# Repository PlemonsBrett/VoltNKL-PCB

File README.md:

# VoltNKL-PCB

This repository contains all information around the Volt NKL (Nav Keyless) Keyboard.

Final Layout:

---

This repository contains:

- Schematics, PCB, and Components under `hardware/`
- Keyboard Layout, Designs, Part Lists, General Ideas under `media/`
- Firmware, and other software specific to a complete build under `software/`

guide used: https://wiki.ai03.com/books/pcb-design/page/pcb-guide-part-4---the-rest-of-the-schematic

MCU used in MacroPad: http://ww1.microchip.com/downloads/en/devicedoc/atmel-7766-8-bit-avr-atmega16u4-32u4_datasheet.pdf

MCU used in Keyboard https://www.st.com/content/st_com/en/products/microcontrollers-microprocessors/stm32-32-bit-arm-cortex-mcus/stm32-mainstream-mcus/stm32f0-series/stm32f0x2.html#tools-software

https://www.st.com/resource/en/datasheet/cd00237391.pdf

Plate Generator: http://www.keyboardcad.com/

Resources: https://keebfolio.netlify.app/tutorials

PCB GUIDE: https://wiki.ai03.com/books/pcb-design/page/pcb-guide-part-1---preparations

Plate Generator: https://kbplate.ai03.com/

Keyboard Firmware Generator: https://kbfirmware.com/

Design Tools: https://keyboard-design.com/tools.html

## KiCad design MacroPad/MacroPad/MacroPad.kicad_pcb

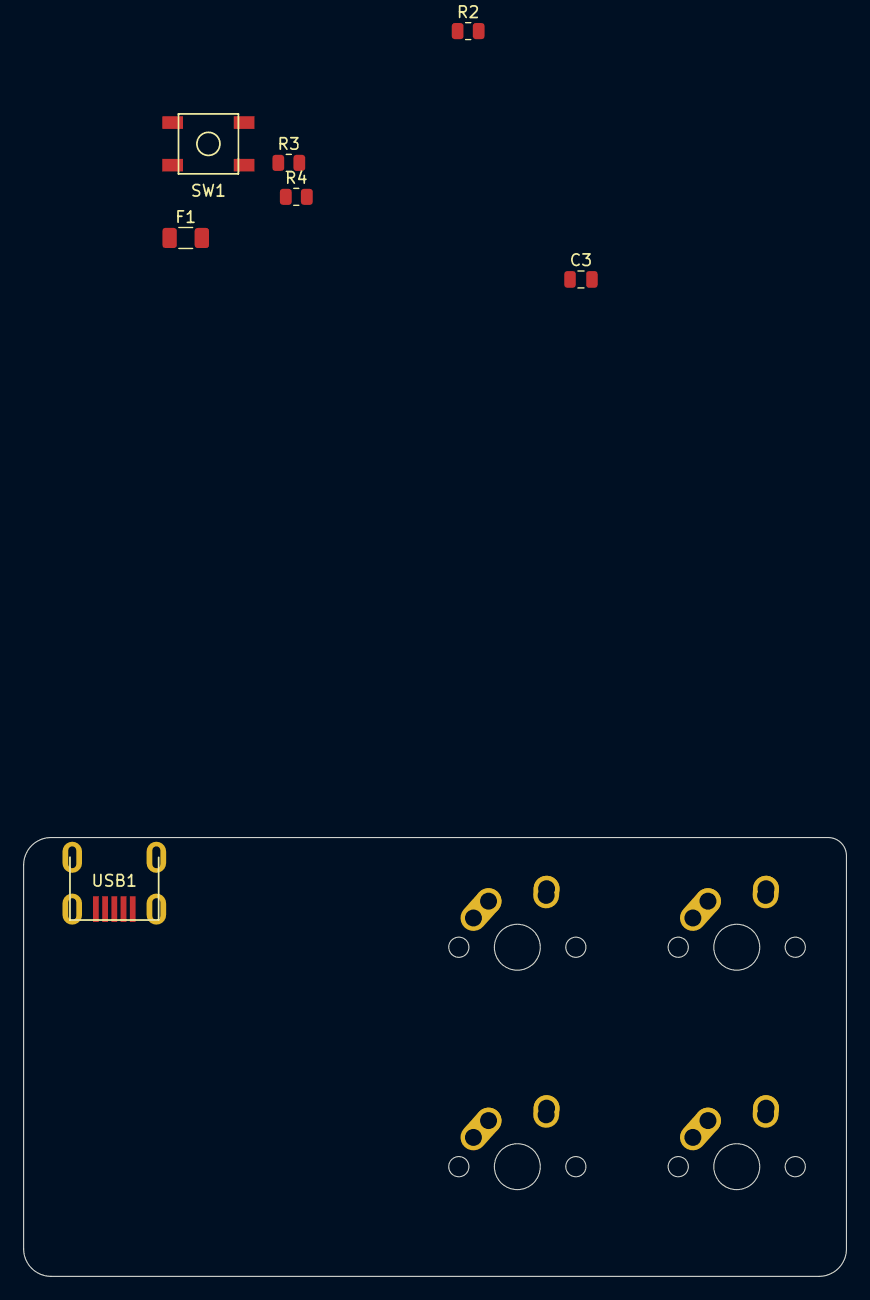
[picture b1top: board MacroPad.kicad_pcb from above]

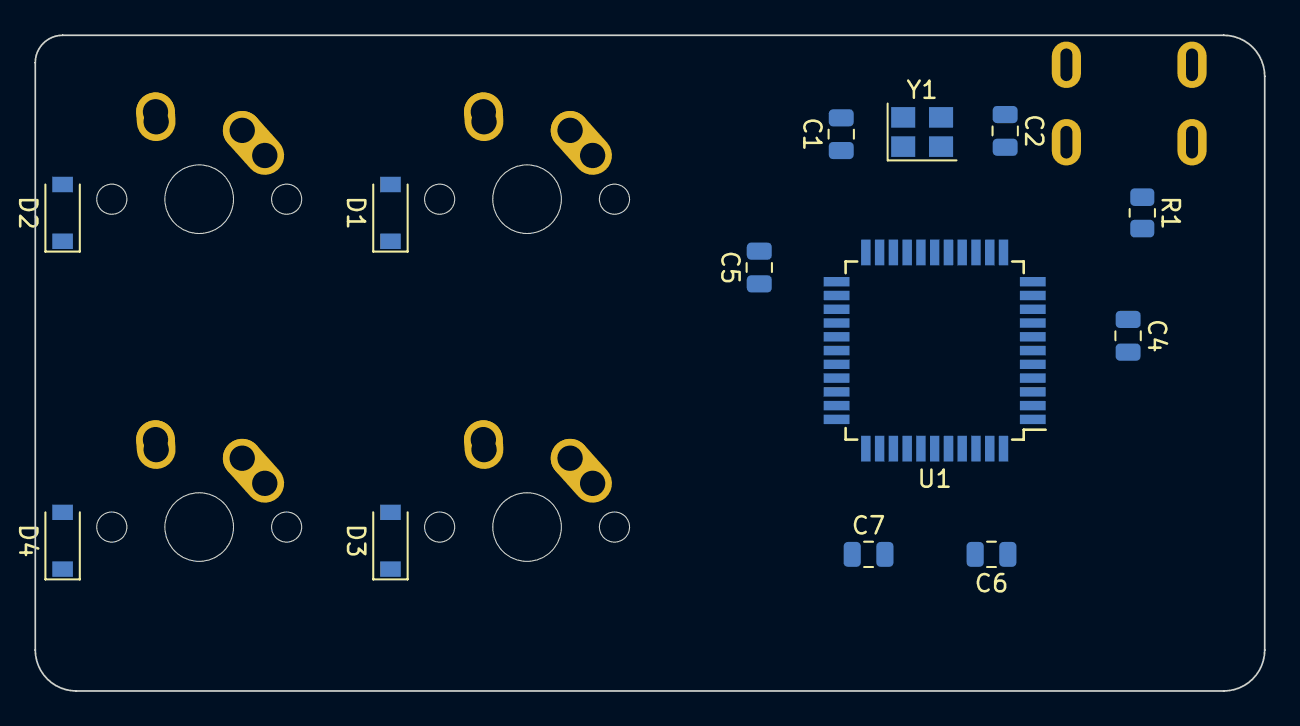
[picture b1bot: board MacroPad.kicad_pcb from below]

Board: 2 copper layers, 71.4 x 38.1 mm, 24 parts (13 on the bottom side), 20 nets, no tracks yet.

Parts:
C1, C2: 22pF; C_0805_2012Metric
C3: 1uF; C_0805_2012Metric
C4, C5, C6: 0.1uF; C_0805_2012Metric
C7: 10uF; C_0805_2012Metric
D1, D2, D3, D4: D_Small; D_SOD-123
F1: 500mA; Fuse_1206_3216Metric
MX1, MX2, MX3, MX4: MX-NoLED; MX-1U-NoLED
R1, R2: 10k; R_0805_2012Metric
R3, R4: 22; R_0805_2012Metric
SW1: SW_Push; SKQG-1155865
U1: ATmega32U4-AU; TQFP-44_10x10mm_P0.8mm
USB1: Molex-0548190589
Y1: 16MHz; Crystal_SMD_3225-4Pin_3.2x2.5mm

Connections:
+5V: C3.2, C4.1, C5.1, C6.1, C7.1, F1.2, R1.2, R2.1, SW1.1, U1.2 (UVCC), U1.7 (VBUS), U1.14 (VCC), U1.24 (AVCC), U1.34 (VCC), U1.44 (AVCC)
COL0: MX1.1 (COL), MX3.1 (COL), U1.29 (PB5)
COL1: MX2.1 (COL), MX4.1 (COL), U1.28 (PB4)
D +: R3.1, USB1.3 (D+)
D -: R4.1, USB1.4 (D-)
GND: C1.2, C2.2, C4.2, C5.2, C6.2, C7.2, U1.5 (UGND), U1.15 (GND), U1.23 (GND), U1.35 (GND), U1.43 (GND), USB1.1 (GND), Y1.2, Y1.4
unnamed: U1.17 (XTAL1), Y1.1
unnamed: C1.1, C2.1, U1.16 (XTAL2), Y1.3
unnamed: C3.1, U1.6 (UCAP)
unnamed: D1.2 (A), MX1.2 (ROW)
unnamed: D2.2 (A), MX2.2 (ROW)
unnamed: D3.2 (A), MX3.2 (ROW)
unnamed: D4.2 (A), MX4.2 (ROW)
unnamed: R1.1, U1.33 (~HWB/PE2)
unnamed: R2.2, SW1.2, U1.13 (~RESET)
unnamed: R3.2, U1.4 (D+)
unnamed: R4.2, U1.3 (D-)
ROW0: D1.1 (K), D2.1 (K), U1.27 (PD7)
ROW1: D3.1 (K), D4.1 (K), U1.30 (PB6)
VCC: F1.1, USB1.6 (SHIELD)

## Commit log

2022-04-16 Add hardware directory
2022-04-16 Add component footprint libraries for kicad
2022-04-16 Add footprint and symbol libraries to kicad
2022-04-17 Add macropad schematics for switch and design testing
2022-04-17 Add layout image to README
2022-04-17 Add footprints for all components on macropad
2022-04-18 Add QMK layout files for firmware
2022-04-18 Remove old layout file
